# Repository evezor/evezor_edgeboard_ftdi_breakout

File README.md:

# evezor_edgeboard_ftdi_breakout

This board uses the standard 6-pin JST-SH connector and breaks out the rx and tx pins and adds 2 bottons for reset and boot pins. 

Source files can be found here: https://github.com/evezor/evezor_edgeboard_ftdi_breakout

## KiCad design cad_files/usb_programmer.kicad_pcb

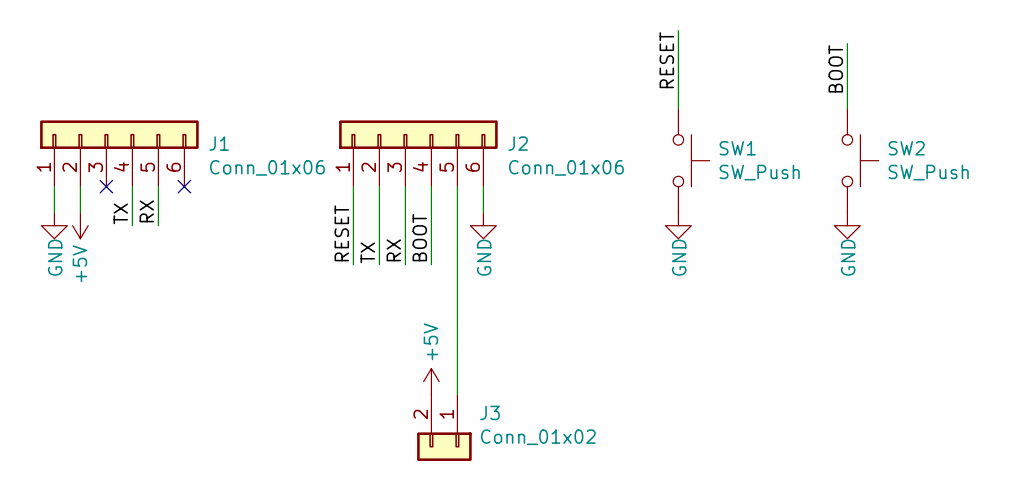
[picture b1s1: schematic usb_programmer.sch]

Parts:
J1: Conn_01x06; PinHeader_1x06_P2.54mm_Horizontal
J2: Conn_01x06; CONN-SH-6P-VERTICAL
J3: Conn_01x02; PinHeader_1x02_P2.54mm_Vertical
SW1, SW2: SW_Push; SWITCH_2x3_SMD_TACTILE_GREEN

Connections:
+5V: J1.2, J3.2
/BOOT: J2.4, SW2.1
/RESET: J2.1, SW1.1
/RX: J1.5, J2.3
/TX: J1.4, J2.2
GND: J1.1, J2.6, SW1.2, SW2.2
unnamed: J2.5, J3.1

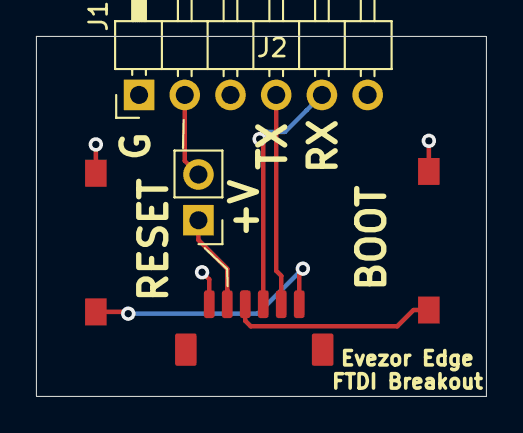
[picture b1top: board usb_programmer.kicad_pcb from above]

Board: 2 copper layers, 25.0 x 20.0 mm, 5 parts (0 on the bottom side), 7 nets.

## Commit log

2023-10-12 init
